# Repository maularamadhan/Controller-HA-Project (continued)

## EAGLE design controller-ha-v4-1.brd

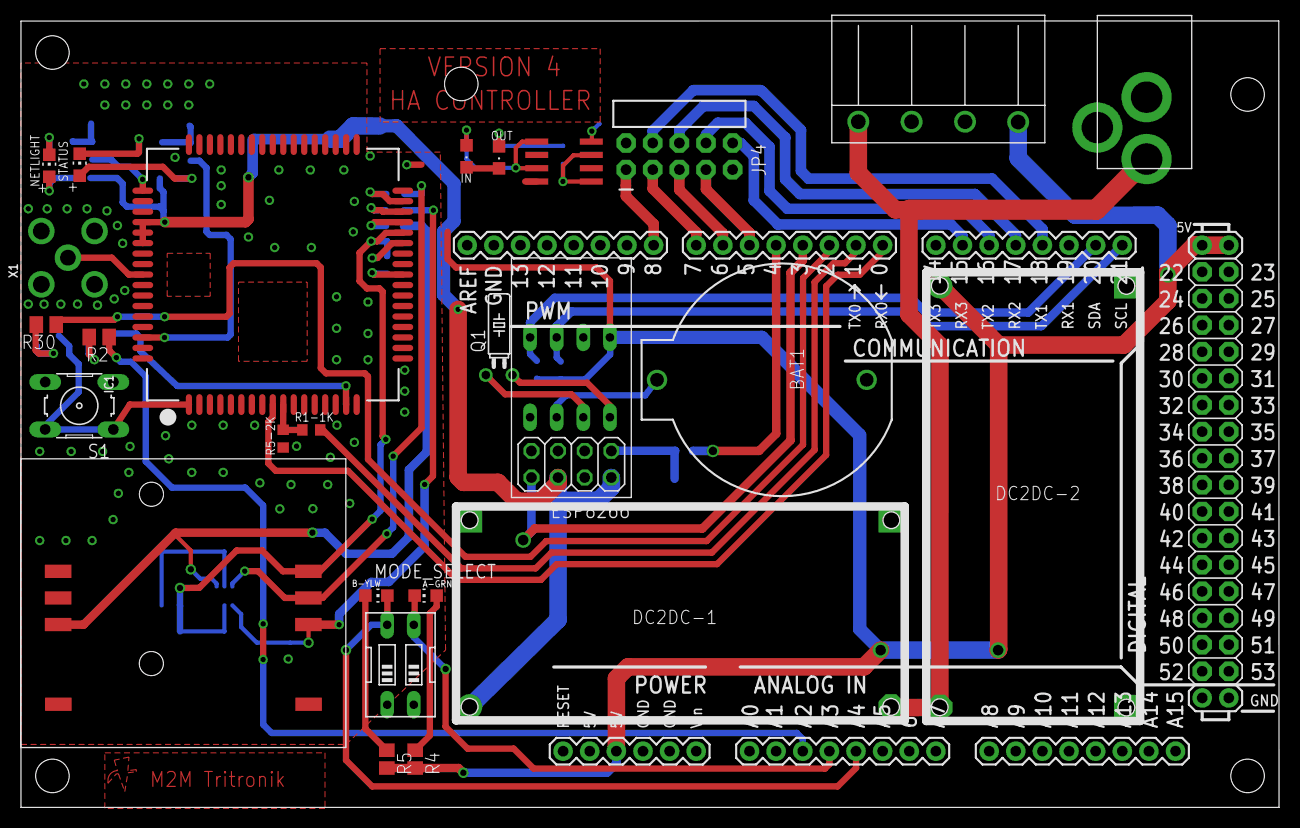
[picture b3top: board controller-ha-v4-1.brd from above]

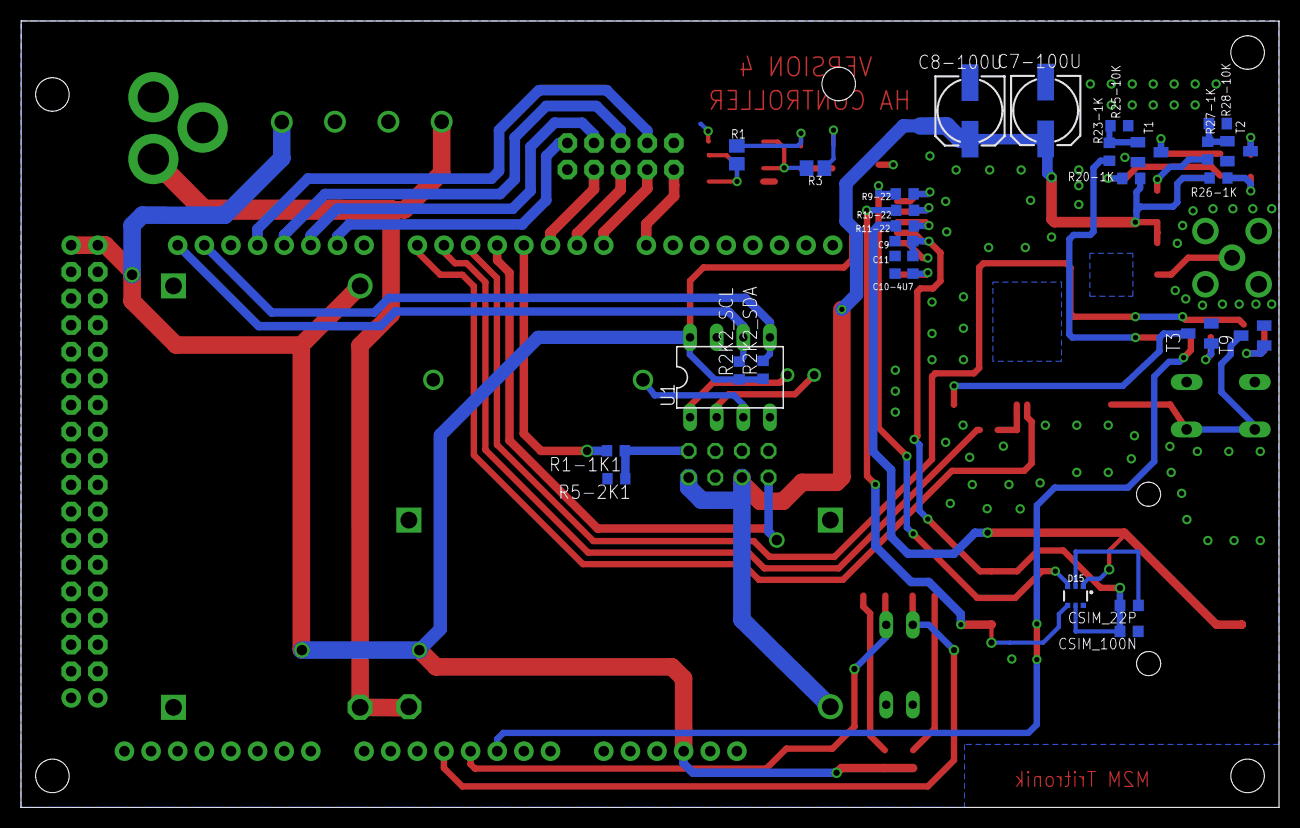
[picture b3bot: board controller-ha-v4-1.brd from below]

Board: 2 copper layers, 120.0 x 75.0 mm, 55 parts (28 on the bottom side), 54 nets.

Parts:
4-WAY_L-TERMINAL: 4-PIN-CON-1759017
A-GRN: green; CHIP-LED0805
ARDUINO_FOOTPRINT: ARDUINO-MEGAFULL; ARDUINO_MEGA
B-YLW: yellow; CHIP-LED0805
BAT1: BATTCOM_20MM_PTH
C7-100U, C8-100U: 100uF; 153CLV-0605
C9: 100nF; C0603
C10-4U7: 4.7nF; C0603
C11: 22pF; C0603
CSIM_22P: 22pF; C0603K
CSIM_100N: 100nF; C0603K
D15: SOT363
DC2DC-1, DC2DC-2: DCDCMODULE
DC_JACKTHM: 2.1MMJACKTHM; PJ-102A
ESP8266: ESP8266
IC1: SIM900_SMT
IC2: LM358MX; SO08
IN: green; CHIPLED_0805
JP4: 2X5-RA
MODE_SELECT: EDG-02
NETLIGHT: green; CHIP-LED0805
OUT: green; CHIPLED_0805
Q1: TC26H
R1, R3: 220; R0805
R1-1K, R1-1K1, R20-1K, R23-1K, R26-1K, R27-1K: 1K; R0603
R2, R30: 120; M0805
R2K2_SCL, R2K2_SDA: 2.2K; R0603
R4, R5: 1K; R0805
R5-2K, R5-2K1: 2K; R0603
R9-22, R10-22, R11-22: 22; R0603
R25-10K, R28-10K: 10K; R0603
S1: B3F-10XX
SIM_HOLDER: SIM_HOLDER_PUSH
STATUS: yellow; CHIP-LED0805
T1, T2, T3, T9: SOT23-BEC
U1: DS1307; DIL08
X1: SMA90_DIP

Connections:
+3V3: C7-100U.+, C8-100U.+, DC2DC-1.VOUT, ESP8266.CHPD, ESP8266.VCC, IC1.P$55, IC1.P$56, IC1.P$57, R20-1K.2, R26-1K.2
+12V: 4-WAY_L-TERMINAL.4, DC2DC-1.VIN, DC2DC-2.VIN, DC_JACKTHM.TIP
CE: ARDUINO_FOOTPRINT.6, JP4.5
CLK: ARDUINO_FOOTPRINT.7, JP4.3
CTRL_SIMRESET: ARDUINO_FOOTPRINT.A2, R2.1
ESP_RX: ESP8266.RXD, R1-1K1.1, R5-2K1.2
ESP_RXX: ARDUINO_FOOTPRINT.4, R1-1K1.2
ESP_TX: ARDUINO_FOOTPRINT.3, ESP8266.TXD
GND: 4-WAY_L-TERMINAL.2, 4-WAY_L-TERMINAL.3, ARDUINO_FOOTPRINT.GND@0, ARDUINO_FOOTPRINT.GND@1, ARDUINO_FOOTPRINT.GND@2, ARDUINO_FOOTPRINT.GND@3, ARDUINO_FOOTPRINT.GND@4, BAT1.2, C7-100U.-, C8-100U.-, C9.2, C10-4U7.2, C11.2, CSIM_22P.1, CSIM_100N.1, D15.2, DC2DC-1.GND#0, DC2DC-1.GND#1, DC2DC-2.GND#0, DC2DC-2.GND#1, DC_JACKTHM.RING, DC_JACKTHM.RING_SW, ESP8266.GND, IC1.P$17, IC1.P$18, IC1.P$29, IC1.P$39, IC1.P$45, IC1.P$46, IC1.P$53, IC1.P$54, IC1.P$58, IC1.P$59, IC1.P$61, IC1.P$62, IC1.P$63, IC1.P$64, IC1.P$65, IC2.4, IN.C, JP4.2, JP4.9, MODE_SELECT.1, MODE_SELECT.2, OUT.C, R5-2K.1, R5-2K1.1, R25-10K.2, R28-10K.2, S1.3, S1.4, SIM_HOLDER.GND, T1.E, T2.E, T3.E, T9.E, U1.4, X1.GND1, X1.GND2, X1.GND3, X1.GND4
unnamed: ARDUINO_FOOTPRINT.1, R1-1K.2
unnamed: IC1.P$31, R11-22.1
unnamed: IC1.P$32, R10-22.1
unnamed: IC1.P$33, R9-22.1
unnamed: C10-4U7.1, IC1.P$26
unnamed: IC1.P$60, X1.ANTENNA
unnamed: R20-1K.1, STATUS.A
unnamed: STATUS.C, T1.C
unnamed: R23-1K.1, R25-10K.1, T1.B
unnamed: NETLIGHT.A, R26-1K.1
unnamed: NETLIGHT.C, T2.C
unnamed: R27-1K.1, R28-10K.1, T2.B
unnamed: R30.2, T9.B
unnamed: R2.2, T3.B
unnamed: Q1.1, U1.2
unnamed: Q1.2, U1.1
unnamed: IC2.1, IC2.3, R1.1
unnamed: BAT1.1, U1.3
unnamed: IC2.5, IC2.7, R3.1
unnamed: OUT.A, R1.2
unnamed: IN.A, R3.2
unnamed: A-GRN.A, R4.1
unnamed: B-YLW.A, R5.1
PL: ARDUINO_FOOTPRINT.5, JP4.7
PWRKEY: ARDUINO_FOOTPRINT.2, R30.1
Q7: ARDUINO_FOOTPRINT.8, IC2.2, JP4.1
SCL: ARDUINO_FOOTPRINT.21, R2K2_SCL.2, U1.6
SDA: ARDUINO_FOOTPRINT.20, R2K2_SDA.2, U1.5
SHCP: ARDUINO_FOOTPRINT.16, JP4.8
SIM_NETLIGHT: IC1.P$52, R27-1K.2
SIM_PWRKEY: IC1.P$1, S1.1, S1.2, T9.C
SIM_RESET: IC1.P$16, T3.C
SIM_RX: IC1.P$10, R1-1K.1, R5-2K.2
SIM_STATUS: IC1.P$66, R23-1K.2
SIM_TX: ARDUINO_FOOTPRINT.0, IC1.P$9
SR_DS: ARDUINO_FOOTPRINT.18, IC2.6, JP4.4
SR_RST: ARDUINO_FOOTPRINT.15, JP4.10
STATE_A: A-GRN.C, ARDUINO_FOOTPRINT.A3, MODE_SELECT.3
STATE_B: ARDUINO_FOOTPRINT.A4, B-YLW.C, MODE_SELECT.4
STCP: ARDUINO_FOOTPRINT.17, JP4.6
USIM_CLK: D15.4, R10-22.2, SIM_HOLDER.CLK
USIM_DATA: D15.1, R11-22.2, SIM_HOLDER.I/O
USIM_RESET: D15.3, R9-22.2, SIM_HOLDER.RST
USIM_VCC: C9.1, C11.1, CSIM_22P.2, CSIM_100N.2, D15.5, IC1.P$30, SIM_HOLDER.VCC
VCC: 4-WAY_L-TERMINAL.1, ARDUINO_FOOTPRINT.5V@0, ARDUINO_FOOTPRINT.5V@1, ARDUINO_FOOTPRINT.5V@2, DC2DC-2.VOUT, IC2.8, R2K2_SCL.1, R2K2_SDA.1, R4.2, R5.2, U1.8
